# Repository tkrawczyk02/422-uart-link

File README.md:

# 422-uart-link

This project contains a schematic and a board for a RS-422 to UART interface converter incorporating a Texas Instruments module DS8921. 
It turned out to be a purely educational eagle project because ready-made converters are far cheaper and widely available in oppostion to DS8921 chips.

This converter was supposed to be used in a wireless long distance bridge, transforming a typical Lowrance cable echosounder to a wireless one, 
which would allow it to be used in a bait boat.

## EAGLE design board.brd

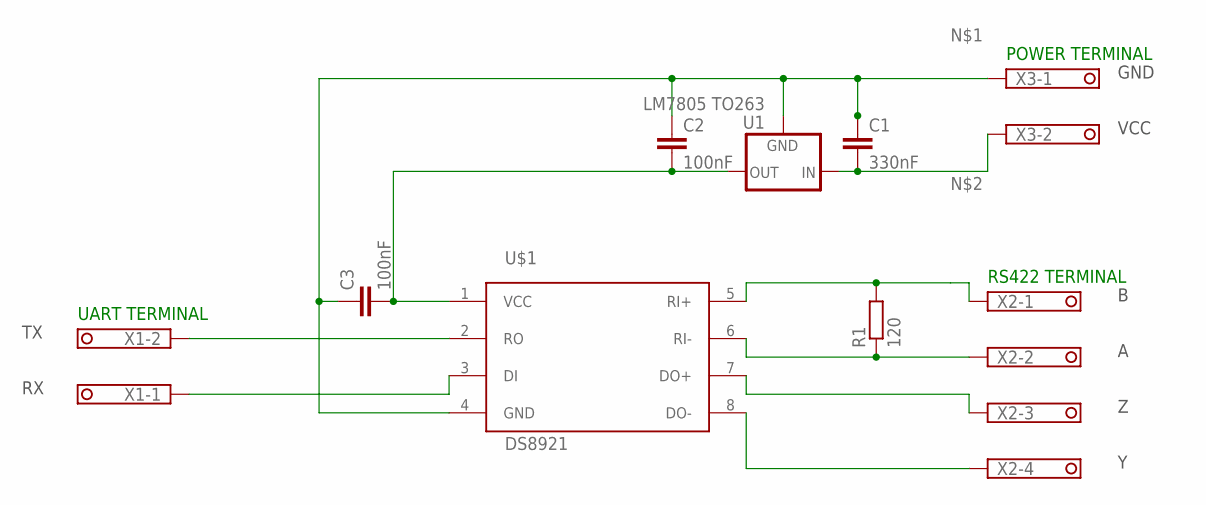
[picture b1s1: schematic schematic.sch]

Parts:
C1: 330nF; C1206K
C2, C3: 100nF; C1206K
R1: 120; R1206
U1: LM7805 TO263; D2PAK
U$1: DS8921; SOIC8
X1, X3: 1751248
X2: 1751264

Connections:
unnamed: C1.1, C2.1, C3.1, U1.2 (GND), U$1.4 (GND), X3.1
unnamed: C1.2, U1.1 (IN), X3.2
unnamed: C2.2, C3.2, U1.3 (OUT), U$1.1 (VCC)
unnamed: U$1.2 (RO), X1.2
unnamed: U$1.3 (DI), X1.1
unnamed: R1.2, U$1.5 (RI+), X2.1
unnamed: U$1.7 (DO+), X2.3
unnamed: U$1.8 (DO-), X2.4
unnamed: R1.1, U$1.6 (RI-), X2.2

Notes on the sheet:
RS422 TERMINAL
UART TERMINAL
POWER TERMINAL
VCC
GND

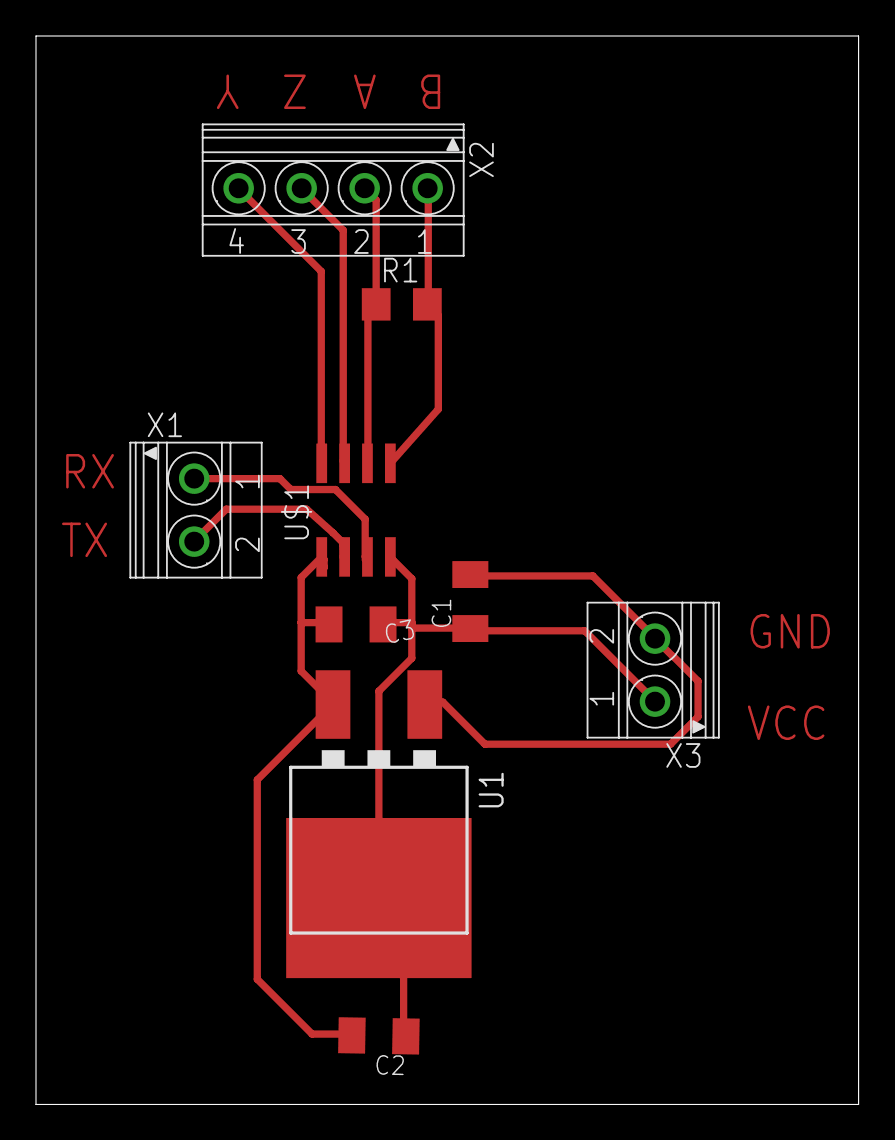
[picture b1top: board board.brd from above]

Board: 2 copper layers, 45.7 x 59.4 mm, 9 parts (0 on the bottom side), 9 nets.
